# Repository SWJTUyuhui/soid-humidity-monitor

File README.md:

# soid-humidity-monitor
monitor soid humidity and post data to onenet

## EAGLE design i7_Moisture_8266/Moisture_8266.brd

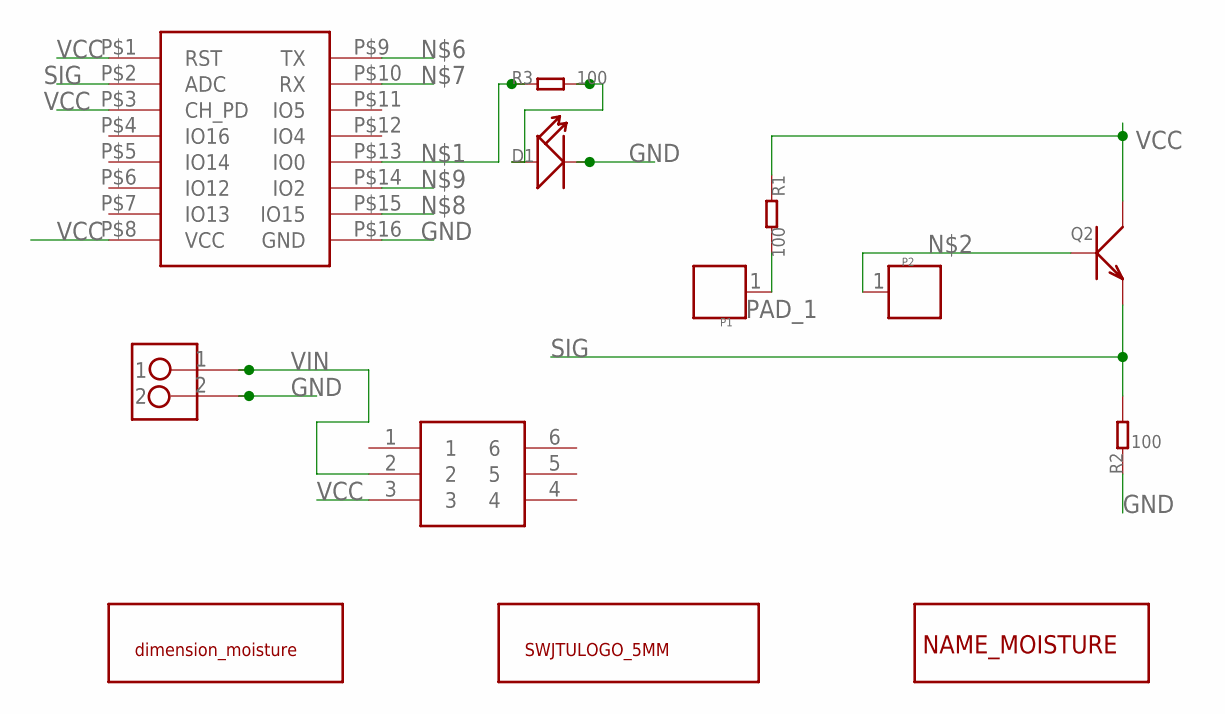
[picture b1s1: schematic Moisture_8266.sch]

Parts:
D1: LED0603; LED-0603
P1, P2: PAD.03; 1P-SMD-0.76X0.76
Q2: TRANSISTOR-NPN-SOT23''; SOT23
R1, R2: 100; 0603
R3: 100; R0603
U$1: MSS-22C02
U$2: SWJTULOGO; SWJTULOGO10*10MM
U$4: NAME_MOISTURE
U$5: HEAD_8266_07
U$6: POWER_3.6V
U$7: DIMENSION_MOISTURE_LONG; MOISTURE_LONG

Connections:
GND: D1.-, R2.1, U$5.P$16 (GND), U$6.2
unnamed: R3.1, U$5.P$13 (IO0)
unnamed: P2.1, Q2.1 (B)
unnamed: D1.+, R3.2
PAD_1: P1.1, R1.2
SIG: Q2.2 (E), R2.2, U$5.P$2 (ADC)
VCC: Q2.3 (C), R1.1, U$1.3, U$5.P$1 (RST), U$5.P$3 (CH_PD), U$5.P$8 (VCC)
VIN: U$1.2, U$6.1

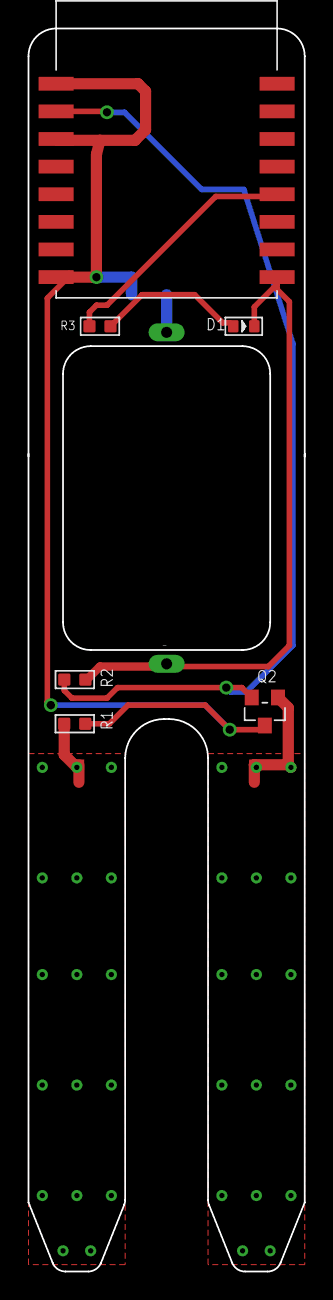
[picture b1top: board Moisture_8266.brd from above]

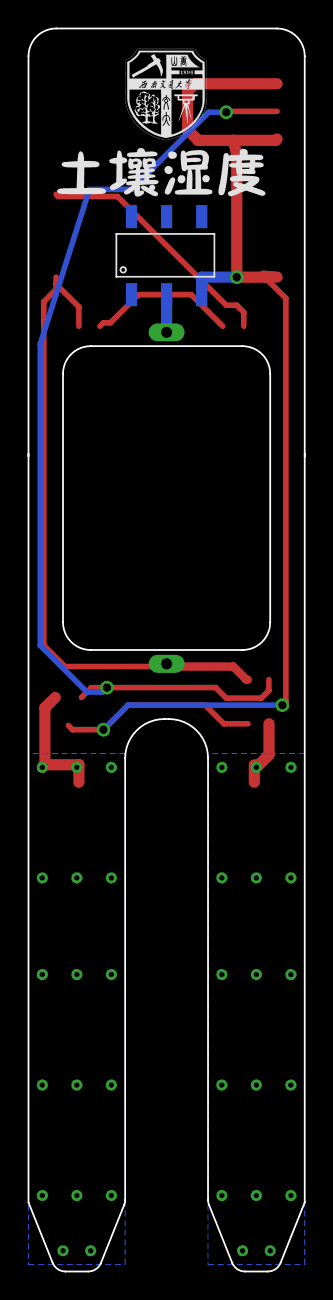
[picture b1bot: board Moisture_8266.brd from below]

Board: 2 copper layers, 20.0 x 90.0 mm, 13 parts (3 on the bottom side), 8 nets.
